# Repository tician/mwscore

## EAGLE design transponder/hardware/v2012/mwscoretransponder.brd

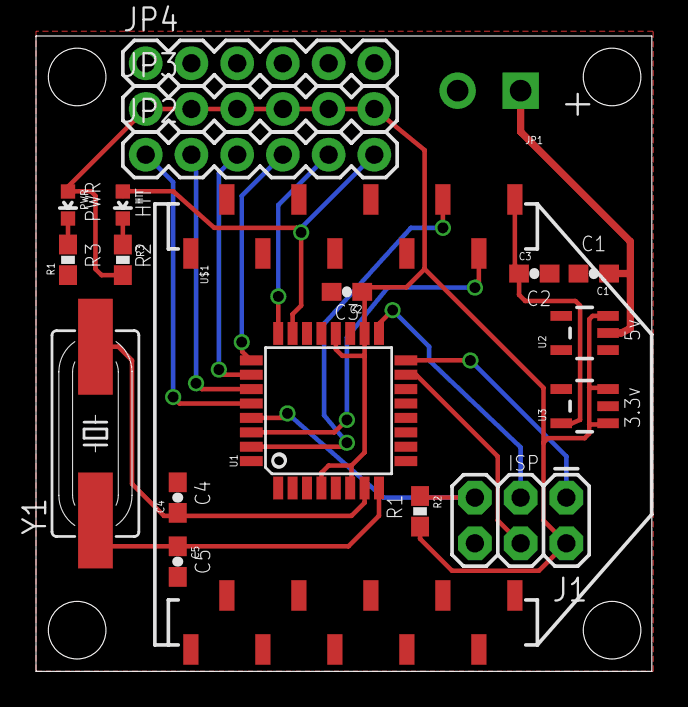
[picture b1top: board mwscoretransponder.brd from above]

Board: 2 copper layers, 34.2 x 35.3 mm, 20 parts (0 on the bottom side), 20 nets.

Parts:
C1, C2, C3, C4, C5: 0603-CAP
HIT: LED-0603
J1: ISP; 2X3
JP1: SCREWTERMINAL-3.5MM-2-NS
JP2, JP3, JP4: 1X06
PWR: LED-0603
R1, R2, R3: 0603-RES
U1: ATMEGA168; TQFP32-08
U2: 5V; SOT23-5
U3: 3.3V; SOT23-5
U$1: XBEE-1B3; XBEE-SMD
Y1: HC49UP

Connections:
3.3V: C3.1, U3.5, U$1.1
5V: C2.1, J1.2, JP3.1, JP3.2, JP3.3, JP3.4, JP3.5, JP3.6, PWR.A, R2.2, R3.2, U1.4, U1.6, U1.18, U1.20, U2.3, U3.1, U3.3
GND: C1.2, C2.2, C3.2, C4.2, C5.2, J1.6, JP1.2, JP4.1, JP4.2, JP4.3, JP4.4, JP4.5, JP4.6, R1.1, U1.3, U1.5, U1.21, U2.1, U3.2, U$1.10
MISO: J1.1, U1.16
MOSI: J1.4, U1.15
unnamed: PWR.C, R1.2
unnamed: C4.1, U1.7, Y1.2
unnamed: C5.1, U1.8, Y1.1
unnamed: HIT.C, R3.1
unnamed: U1.30, U$1.2
unnamed: U1.31, U$1.3
RESET: J1.5, R2.1, U1.29
SCK: J1.3, U1.17
TP0: JP2.4, U1.25
TP1: JP2.3, U1.26
TP2: JP2.2, U1.27
TP3: JP2.1, U1.28
TPOUT: JP2.5, U1.24
TPOUT2: HIT.A, JP2.6, U1.23
VCC: C1.1, JP1.1, U2.2
